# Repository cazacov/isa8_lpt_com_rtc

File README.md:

# ISA8 LPT COM RTC

An 8-bit ISA expansion card providing a parallel port, two serial ports, and a battery-backed real-time clock for retro PC/XT systems.

The card was designed with a help of GitHub Copilot.

## Prototype
See [prototype.md](./prototype.md) - Learn how to decode address, control RTC chip and design GAL firmware.

Vibe soldering with LLM.

## Features

- **Parallel Port (PRN)** — UM82C11-C, DB-25 connector, Centronics-compatible
- **2 × Serial Port (COM)** — 16450/16550-compatible UARTs, RS-232 levels via GD75232N
- **Real-Time Clock (RTC)** — DS12885 with CR2032 battery backup and CMOS RAM
- **Single-chip address decoding** — ATF22V10 PLD, no additional logic gates
- **Fully jumper-configurable** — port addresses and IRQs
- **Socket-based device enable/disable** — devices disabled by removing chip from socket; 10k pull-up resistor network on data bus ensures clean 0xFF reads for empty sockets

## Target Systems

- IBM PC/XT and compatibles (8088/8086)
- Compatible with [8088 BIOS](https://github.com/skiselev/8088_bios)
- DOS and early Windows

## Design Specifications

### ISA Bus Interface

- 8-bit data bus (D0–D7)
- Standard ISA 8-bit (62-pin) edge connector
- +5 V, +12 V, −12 V power rails from bus

### Parallel Port (PRN)

- UM82C11-C printer adapter interface chip
- DB-25 connector, standard Centronics-compatible
- Configurable base address: 0x378 (LPT1) or 0x278 (LPT2)
- Configurable interrupt: IRQ7 or IRQ5
- Active-low chip select: PRN_CS#

### Serial Ports (UART)

Both ports use 16450/16550-compatible UARTs with RS-232 level shifting (GD75232N or equivalent). CS0 and CS1 are tied to GND; CS2 is the active-low chip select driven by the PLD.

| Port | Connector | Base Address Options | IRQ Options | CS Signal |
|------|-----------|---------------------|-------------|-----------|
| COM1 | DB-9 | 0x3F8 or 0x2F8 | IRQ4 or IRQ3 | COM1_CS# |
| COM2 | 2×5 header | 0x3E8 or 0x2E8 | IRQ4 or IRQ3 | COM2_CS# |

### Real-Time Clock (RTC)

- DS12885 RTC chip with CMOS RAM for BIOS settings
- CR2032 battery backup
- Fixed I/O ports 0x70 (address) / 0x71 (data)
- Intel bus timing (MOT pin left unconnected; internal 20kΩ pull-down selects Intel mode)
- Configurable interrupt: IRQ2/9, IRQ5, IRQ6, or IRQ7
- IRQ polarity inversion: DS12885 IRQ output is active-low open-drain; an NPN transistor (Q1, 2N3904) with a 330Ω series current-limiting resistor converts it to the active-high signal expected by the ISA bus 8259A PIC (see [design.md](design.md) Section 6 for circuit details)
- On PC/XT (single 8259A), the IRQ2 jumper position triggers IRQ2 (INT 0Ah); on AT-class systems (cascaded 8259A), the same physical IRQ2 line is routed to the slave PIC as IRQ9 (INT 71h), which the BIOS redirects to INT 0Ah for compatibility
- Multiplexed address/data bus: CPU writes register address to port 0x70, then reads/writes data at port 0x71 (see [design.md](design.md) Section 5 for interface details, timing diagrams, and PLD equations)

### Oscillators

| Ref | Frequency | Purpose |
|-----|-----------|---------|
| Y1 | 32.768 kHz | RTC crystal |
| Y2 | 1.8432 MHz | UART clock oscillator |

### Data Bus Buffering

A 74HCT245 bidirectional transceiver decouples all peripheral data pins from the ISA bus:

- **ISA side** (A1–A8, pins 2–9) — connected to ISA D0–D7
- **Card side** (B1–B8, pins 11–18) — connected to RTC, UART, and PRN data pins; 8×10k pull-up resistor network to VCC ensures defined HIGH state when no device drives the bus (empty sockets read as 0xFF)
- **DIR** — connected to IOR# (IOR#=0 → B-to-A read; IOR#=1 → A-to-B write)
- **G#** — active-low enable driven by ATF22V10

### Address Decoding

A single ATF22V10 PLD decodes all port addresses and generates chip-select signals for every peripheral, plus the bus buffer enable and the RTC address strobe. No additional logic gates are required. Jumper inputs to the PLD allow per-device address and enable configuration.

See [design.md](design.md) for detailed PLD equations, pin assignments, and CUPL source.

### Jumper Configuration

#### Address Selection (3-pin headers: VCC / signal / GND)

| Jumper | Cap 1-2 (HIGH) | Cap 2-3 (LOW) |
|--------|----------------|---------------|
| J1 (COM1 Addr) | 0x3F8 (COM1) | 0x2F8 (COM2) |
| J3 (COM2 Addr) | 0x3E8 (COM3) | 0x2E8 (COM4) |
| J5 (PRN Addr) | 0x378 (LPT1) | 0x278 (LPT2) |

#### IRQ Selection (3-pin headers)

| Jumper | Position 1 | Position 2 |
|--------|-----------|-----------|
| J2 (COM1 IRQ) | IRQ4 | IRQ3 |
| J4 (COM2 IRQ) | IRQ4 | IRQ3 |
| J6 (PRN IRQ) | IRQ7 | IRQ5 |
| J7 (RTC IRQ) | IRQ2/9 / IRQ5 / IRQ6 / IRQ7 (1×5 header) | — |

#### RTC CMOS Clear

J8 is a 2-pin header connected between DS12885 RCLR# (pin 21) and GND. The RCLR# pin has an internal pull-up inside the DS12885. Momentarily shorting J8 with a jumper cap (while the system is powered off) clears all CMOS RAM and RTC registers to defaults.

#### Device Enable/Disable

Devices are enabled/disabled by installing or removing the chip from its DIP socket. A 10k×8 pull-up resistor network on the 74HCT245 B-side ensures that empty sockets read as 0xFF, which is the expected response for absent I/O devices. Software detection (e.g., BIOS UART scratch register test) correctly identifies the device as absent.

The RTC is always enabled (no disable mechanism).

## Manufacturing Notes

- **Board thickness:** 1.6 mm
- **Copper weight:** 1 oz (35 μm)
- **Surface finish:** HASL or ENIG
- **Solder mask / silkscreen:** any color; white silkscreen on top
- **Components:** through-hole
- **Form factor:** standard ISA 8-bit card dimensions
- **Connectors:** bracket-mounted DB-25 and DE-9; CR2032 battery holder

## Getting Started

### Required Software

- [KiCad](https://www.kicad.org/) 9.0 or later
- [GALasm](https://github.com/daveho/GALasm) to compile firmware
- A PLD programmer (e.g. TL866II+) for the ATF22V10
- Git

### Opening the Project

1. Clone the repository
2. Open `KiCad/V2/ISA8_LPT_COM_RTC.kicad_pro` in KiCad
3. Schematic: `KiCad/V2/ISA8_LPT_COM_RTC.kicad_sch`
4. PCB layout: `KiCad/V2/ISA8_LPT_COM_RTC.kicad_pcb`

### Testing

1. Visually inspect for solder bridges; continuity-test power rails
2. Install card in an ISA slot
3. Verify I/O port addressing with DEBUG or a diagnostic utility
4. Test serial ports with a loopback plug or terminal program
5. Test parallel port with a printer or loopback connector
6. Verify RTC keeps time after power-off (battery backup)
7. Confirm interrupt operation for each device

## KiCad

Third party libraries should be stored in locations referenced with environment variables:
- **KICADLIB_SKISELEV** [Sergey Kiselev's library](https://github.com/skiselev/my_kicad_library)
- **KICADLIB_VICTOR** [Victor's (my) library](https://github.com/cazacov/VictorLib)

## Troubleshooting

| Symptom | Check |
|---------|-------|
| Card not detected | ISA slot seating, power rails |
| Address conflicts | Reconfigure base address jumpers, ensure ATF22V10 firmware is programmed properly |
| IRQ conflicts | Change IRQ jumper settings |
| RTC loses time | Replace CR2032 battery |
| Serial errors | Baud rate, RS-232 cable/levels |
| Parallel port issues | Cable, port mode |

## Project Files

| File | Description |
|------|-------------|
| `KiCad/V2/ISA8_LPT_COM_RTC.kicad_pro` | KiCad project |
| `KiCad/V2/ISA8_LPT_COM_RTC.kicad_sch` | Schematic |
| `KiCad/V2/ISA8_LPT_COM_RTC.kicad_pcb` | PCB layout |
| `design.md` | Implementation plan — PLD equations, pin maps, CUPL source |
| `pld/ISA8_DECODE.pld` | CUPL source for ATF22V10 |
| `pld/ISA8_DECODE.jed` | Compiled JEDEC fuse map |

## Datasheets

- [DS12885 / DS12C887A (RTC)](https://www.analog.com/media/en/technical-documentation/data-sheets/DS12885-DS12C887A.pdf)

## Version History

| Version | Notes |
|---------|-------|
| V2 | Current design iteration |
| V1 | Initial design (see `KiCad/V1/`) |

## Contributing

1. Document all schematic changes
2. Update PCB layout accordingly
3. Run DRC and ERC in KiCad
4. Update documentation as needed

## Credits

- [Sergey Kiselev's projects](https://github.com/skiselev)
- [Aitor Gómez García's RTC8088 project](https://github.com/spark2k06/RTC8088)

## License

MIT

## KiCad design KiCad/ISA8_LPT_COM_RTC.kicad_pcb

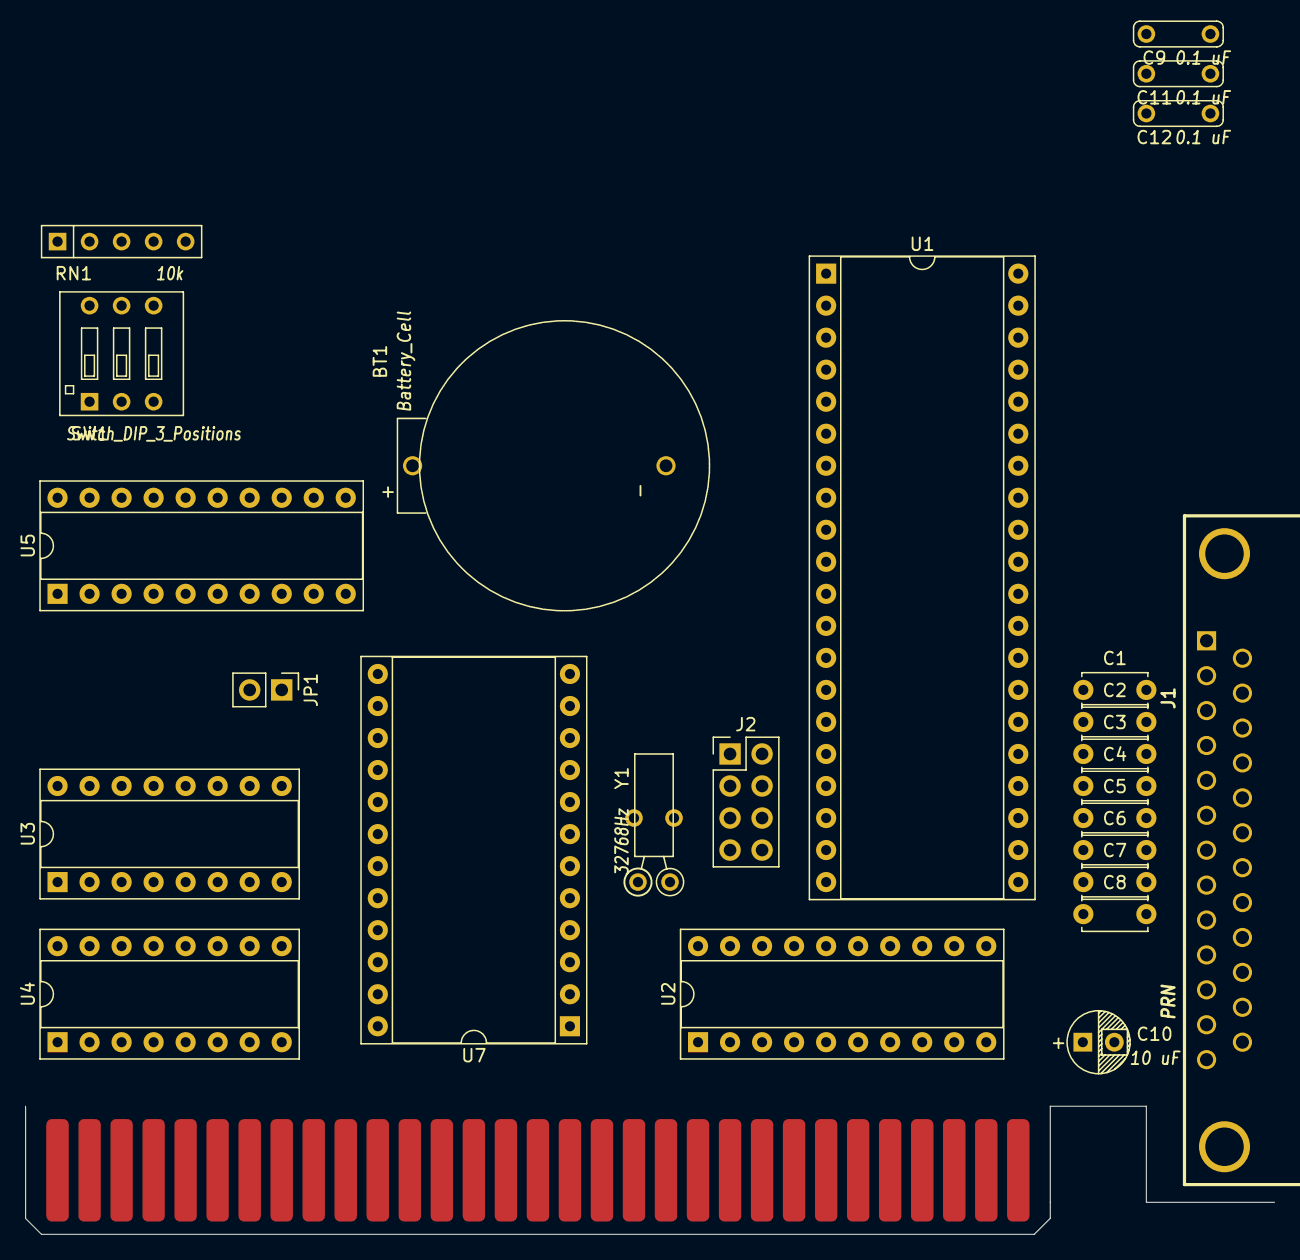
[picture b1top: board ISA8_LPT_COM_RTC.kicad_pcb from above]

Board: 2 copper layers, 26 parts (0 on the bottom side), 68 nets, no tracks yet.

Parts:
BT1: Battery_Cell; Battery_Holder_CR2032_Mouser_122-2420-GR
BUS1: BUSPC_DEV; Conn_Edge_PCB_ISA8
C1, C2, C3, C4, C5, C6, C7, C8: 2200pF; C_Disc_D5.0mm_W2.5mm_P5.00mm
C9, C11, C12: 0.1 uF; Cap_Cer_508
C10: 10 uF; Cap_Elec_Radial_5mm_2.5mm
J1: PRN; Conn_Dsub_DB25F
J2: PRN_Conf; PinHeader_2x04_P2.54mm_Vertical
JP1: Clear CMOS; PinHeader_1x02_P2.54mm_Vertical
RN1: 10k; Conn_SIL5
SW1: Switch_DIP_3_Positions
U1: 82C11; DIP-40_W15.24mm_Socket
U2: 74HCT245; DIP-20_W7.62mm_Socket
U3, U4: 74HCT138; DIP-16_W7.62mm_Socket
U5: ATF16V8B; DIP-20_W7.62mm_Socket
U7: DS12885; DIP-24_W15.24mm_Socket
Y1: 32768Hz; Crystal_32K_Horiz

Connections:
/0x278: J2.5, U3.13 (~Y2)
/0x378: J2.7, U3.12 (~Y3)
/A0: BUS1.62 (SA0), U1.38 (A0), U5.1 (I/CLK)
/A1: BUS1.61 (SA1), U1.39 (A1)
/A2: BUS1.60 (SA2), U5.2 (I1)
/A3: BUS1.59 (SA3), U4.1 (A0), U5.3 (I2)
/A4: BUS1.58 (SA4), U3.2 (A1), U5.4 (I3)
/A5: BUS1.57 (SA5), U4.2 (A1), U5.5 (I4)
/A6: BUS1.56 (SA6), U4.3 (A2), U5.6 (I5)
/A7: BUS1.55 (SA7), U3.3 (A2), U5.7 (I6)
/A8: BUS1.54 (SA8), U3.1 (A0), U5.8 (I7)
/A9: BUS1.53 (SA9), U3.6 (E2), U5.9 (I8)
/AEN: BUS1.42 (AEN), U3.4 (~E0), U5.17 (I/O3)
/AS0: RN1.2 (R1), SW1.6, U5.19 (I/O1)
/AS1: RN1.3 (R2), SW1.5, U5.18 (I/O2)
/AS2: RN1.4 (R3), SW1.4, U5.11 (I9/~OE)
/BUSY: J1.11, U1.25 (BUSY)
/D0: BUS1.40 (SD0), U2.18 (B0), U7.4 (AD0)
/D1: BUS1.39 (SD1), U2.17 (B1), U7.5 (AD1)
/D2: BUS1.38 (SD2), U2.16 (B2), U7.6 (AD2)
/D3: BUS1.37 (SD3), U2.15 (B3), U7.7 (AD3)
/D4: BUS1.36 (SD4), U2.14 (B4), U7.8 (AD4)
/D5: BUS1.35 (SD5), U2.13 (B5), U7.9 (AD5)
/D6: BUS1.34 (SD6), U2.12 (B6), U7.10 (AD6)
/D7: BUS1.33 (SD7), U2.11 (B7), U7.11 (AD7)
/IOR: BUS1.14 (IOR), U1.7 (~IOR), U5.13 (I/O7)
/IOW: BUS1.13 (IOW), U1.6 (~IOW), U5.12 (I/O8)
/IRQ6: BUS1.22 (IRQ6), J2.1
/IRQ7: BUS1.21 (IRQ7), J2.3
/PE: J1.12, U1.27 (PE)
/PRN_CS: J2.6, J2.8, U1.18 (~CS), U2.19 (CE)
/PRN_IRQ: J2.2, J2.4, U1.17 (IRQ)
/P_DATA0: C1.2, J1.2, U1.37 (P0)
/P_DATA1: C2.2, J1.3, U1.36 (P1)
/P_DATA2: C3.2, J1.4, U1.35 (P2)
/P_DATA3: C4.2, J1.5, U1.34 (P3)
/P_DATA4: C5.2, J1.6, U1.33 (P4)
/P_DATA5: C6.2, J1.7, U1.32 (P5)
/P_DATA6: C7.2, J1.8, U1.31 (P6)
/P_DATA7: C8.2, J1.9, U1.30 (P7)
/RESET: BUS1.2 (RESET), U1.5 (RST)
/RTCALE: U5.14 (I/O6), U7.14 (AS)
/RTCRD: U5.16 (I/O4), U7.17 (DS)
/RTCWR: U5.15 (I/O5), U7.15 (R/~W)
/SLCK: J1.13, U1.28 (SLCT)
/~ACK: J1.10, U1.26 (~ACK)
/~AUTOFD: J1.14, U1.23 (~AUTOFD)
/~ERROR: J1.15, U1.29 (~ERROR)
/~INIT: J1.16, U1.22 (~INIT)
/~RTC_IRQ: RN1.5 (R4), U7.19 (~IRQ)
/~SCLK: J1.17, U1.21 (~SLCT)
/~STROB: J1.1, U1.24 (~STROB)
GND: BT1.2 (-), BUS1.1 (GND), BUS1.10 (GND), BUS1.31 (GND), C1.1, C2.1, C3.1, C4.1, C5.1, C6.1, C7.1, C8.1, C9.2, C10.2, C11.2, C12.2, J1.18, J1.19, J1.20, J1.21, J1.22, J1.23, J1.24, J1.25, JP1.2 (B), SW1.1, SW1.2, SW1.3, U1.19 (~POE), U1.20 (Vss), U2.10 (GND), U3.8 (GND), U4.4 (~E0), U4.5 (~E1), U4.8 (GND), U5.10 (GND), U7.12 (GND), U7.13 (~CS), U7.16 (GND), Y1.3
unnamed: BT1.1 (+), U7.20 (VBAT)
unnamed: JP1.1 (A), U7.21 (~RCLR)
unnamed: U1.9 (D0), U2.2 (A0)
unnamed: U1.10 (D1), U2.3 (A1)
unnamed: U1.11 (D2), U2.4 (A2)
unnamed: U1.12 (D3), U2.5 (A3)
unnamed: U1.13 (D4), U2.6 (A4)
unnamed: U1.14 (D5), U2.7 (A5)
unnamed: U1.15 (D6), U2.8 (A6)
unnamed: U1.16 (D7), U2.9 (A7)
unnamed: U1.8 (DIR), U2.1 (A->B)
unnamed: U3.5 (~E1), U4.7 (~Y7)
unnamed: U7.2 (X1), Y1.1
unnamed: U7.3 (X2), Y1.2
VCC: BUS1.3 (VCC), BUS1.29 (VCC), C9.1, C10.1, C11.1, C12.1, RN1.1 (common), U1.40 (VDD), U2.20 (VCC), U3.16 (VCC), U4.6 (E2), U4.16 (VCC), U5.20 (VCC), U7.18 (~RESET), U7.24 (VCC)

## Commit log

2024-11-24 Added 82C11 chip and printer interface
2024-11-24 Set footprints
2024-12-14 Design COM ports
2026-02-07 Refactoring
2026-02-14 Add spec
2026-02-14 Create plans
2026-02-21 Vibe coding
2026-02-22 Working prototype.
2026-02-22 Document IRQ inverter
2026-02-24 Draw diagram
2026-02-24 Add prototype photo
